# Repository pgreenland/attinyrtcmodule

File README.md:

# ATTinyRTCModule

This repository contains my attempt at a real-time clock (RTC) replacement, specially for the Mac SE/30, untested (yet should work :-P) on others, using the Microchip ATTiny85.

It's specifically aimed at SE/30's that have suffered damage to their RTC circuitry due to battery leaks.

It therefore doesn't require a battery, storing the PRAM contents in the ATTiny's integrated EEPROM.

It also doesn't require a crystal, using the ATTiny's integrated RC oscillator as its clock source.

It should work (although hasn't been tested) in a mac with a working RTC battery. If desired the EEPROM backup of the settings and time can be disabled via commenting out the definition `ENABLE_EEPROM`.

An effort has been made to limit the EEPROM writes. With only updates being written, and update only being considered when the RTC is marked as read-only by the host. However it isn't clear how long the EEPROM will last in the ATTiny's using this approach. Time will tell.

It's based on the good work by other folks:

https://www.reddit.com/r/VintageApple/comments/91e5cf/couldnt_find_a_replacement_for_the_rtcpram_chip/
https://pastebin.com/baPZ4nN4
https://github.com/quorten/macsehw/blob/master/firmware/rtc/MacRTC.c

The ATTiny85 was identified previously as a candidate for a drop-in replacement for some of the classic Mac family of RTC chips.

Previous versions of the firmware focused on the Mac Plus, which has a serial clock of between 1 and 20Khz (based on comments in the code).

The Mac SE/30 has a serial clock of 250Khz, requiring a substantial rewrite to get things working.

This version makes use of the universal serial interface module (USI) to ensure the original timing of the Apple RTC is always met.

My original drop-in replacement attempt [ATTinyRTC](https://github.com/pgreenland/attinyrtc) worked but was often a little close to violating the protocol timing. Using the USI module these problems are avoided and the timings exhibited by the original Apple RTC module are met.

See my blog for additional notes on how the software works / its development:

[New Timepiece for a Classic Mac - Part 1](http://www.quantulum.co.uk/blog/new-timepiece-for-a-classic-mac-part-1/)

[New Timepiece for a Classic Mac - Part 2](http://www.quantulum.co.uk/blog/new-timepiece-for-a-classic-mac-part-2/)

## Hardware

PCB may be ordered from yoru favorite supplier.

The BOM for this project was ordered from RS Components in the UK and consists of the following:

| **Reference** | **Part**                                                                                           | **Quantity** | **RS Part No** |
|---------------|----------------------------------------------------------------------------------------------------|--------------|----------------|
| U1            | Microchip ATTINY85-20SU, 8bit AVR Microcontroller, ATtiny85, 20MHz, 8 kB Flash, 8-Pin EIAJ SOIC    | 1            | 133-1674       |
| Y1            | Abracon 16MHz Crystal Unit ±20ppm SMD 4-Pin 3.2 x 2.5 x 0.8mm                                      | 1            | 171-2803       |
| C1,C2         | KEMET, 0805 (2012M) 18pF Multilayer Ceramic Capacitor MLCC 50V dc ±5% , SMD C0805C180J5GACTU       | 2            | 648-0935       |
| C3            | KYOCERA AVX, 0805 (2012M) 100nF Multilayer Ceramic Capacitor MLCC 50V dc ±10% , SMD 08055C104KAT2A | 1            | 464-6688       |

## Building

1. Ensure avg-gcc, cmake, make and avrdude are installed.

2. Build with cmake
   ```
   cd software
   mkdir build
   cd build
   cmake ..
   make
   ```

3. Flash
   ```
   make upload
   make upload_eeprom
   ```

4. Set fuses
   ```
   make fuses
   ```

### Note

The programmer I'm using is a usbasp programmer, search eBay for USBasp, they all seem pretty much the same. Remember to head over to [USBasp](https://www.fischl.de/usbasp/) to drop them a tip. Alternatively any programmer supported by avrdude can be selected via configuration in the CMake file.

If flashing using the external pins, remember that PB0 and PB1 are swapped (I definately didn't make that mistake).

As part of setting fuses the reset pin is reconfigured as GPIO.

Once this has been done the only way to re-program the chip is by using high voltage programming.

During development, as a workaround I've been re-assigning one of the unused crystal pins to fullfil the role of the PB5, with the help of a small adapter. Thereby allowing standard ICSP programming with no high voltage funny business required.

After the initial programming I found [this guide](https://www.electronics-lab.com/recover-bricked-attiny-using-arduino-as-high-voltage-programmer/) helpful. Using a spare Arduino and minimal components to rewrite the fuses using HV programming, such that the reset pin is again enabled and regular ICSP programming can be performed again.

If resetting fuses using the external pins, note that PB0 and PB1 are swapped as noted above. Also note that PB3 is not accessible via the headers and must be accessed directly on the ATTiny.

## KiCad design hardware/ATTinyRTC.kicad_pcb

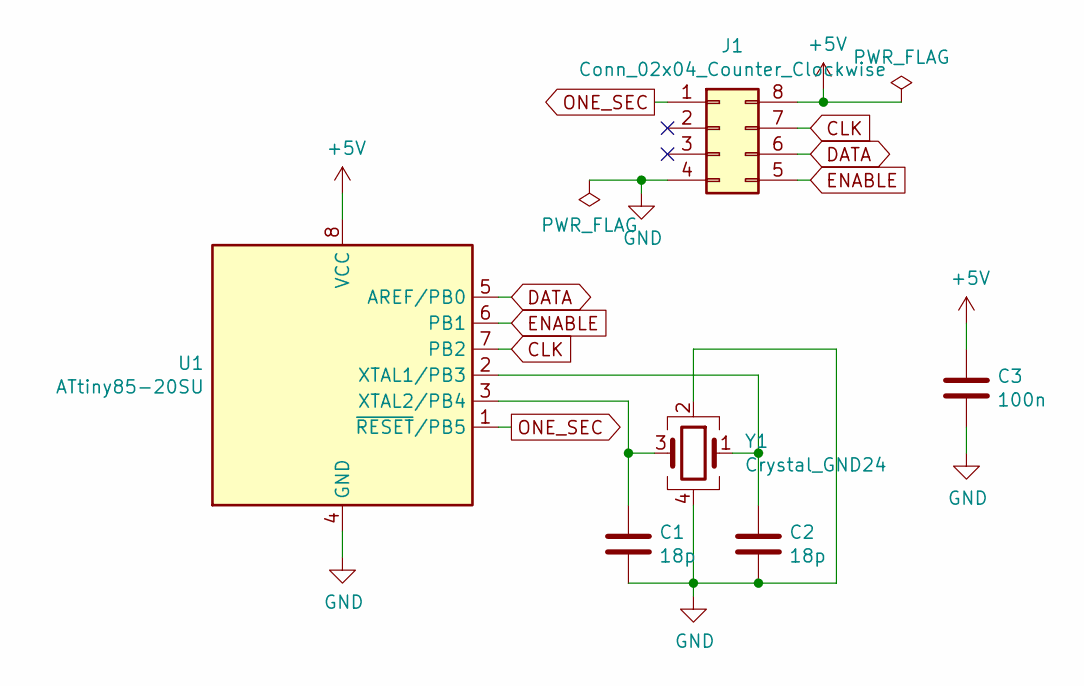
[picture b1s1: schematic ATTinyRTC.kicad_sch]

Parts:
C1, C2: 18p; C_0805_2012Metric
C3: 100n; C_0805_2012Metric
J1: Conn_02x04_Counter_Clockwise; DIP-8_W7.62mm
U1: ATtiny85-20SU; SOIC-8W_5.3x5.3mm_P1.27mm
Y1: Crystal_GND24; Crystal_SMD_Abracon_ABM8G-4Pin_3.2x2.5mm

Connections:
+5V: C3.1, J1.8, U1.8 (VCC)
CLK: J1.7, U1.7 (PB2)
DATA: J1.6, U1.5 (AREF/PB0)
ENABLE: J1.5, U1.6 (PB1)
GND: C1.2, C2.2, C3.2, J1.4, U1.4 (GND), Y1.2, Y1.4
unnamed: C1.1, U1.3 (XTAL2/PB4), Y1.3
unnamed: C2.1, U1.2 (XTAL1/PB3), Y1.1
ONE_SEC: J1.1, U1.1 (~RESET/PB5)

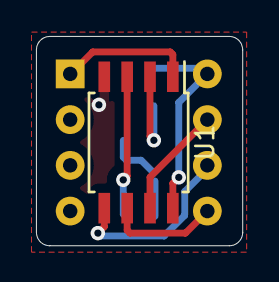
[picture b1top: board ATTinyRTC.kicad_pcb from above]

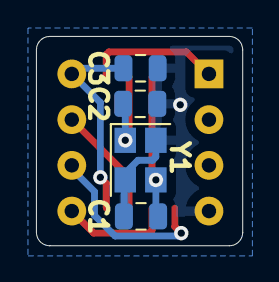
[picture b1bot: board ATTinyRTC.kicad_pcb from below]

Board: 2 copper layers, 11.5 x 11.6 mm, 6 parts (4 on the bottom side), 8 nets.

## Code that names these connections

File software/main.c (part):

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/* Define to have write only test register readable, returning 0xA5 and 0x5A on alternate reads */
//#define TEST_REG_READ_DUMMY_VALUE

/* Define to output timing pulses on PB3 */
//#define TIMING_ENABLED

/* ---------------------- */
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/*
RTC Pinout -> ATTiny85 pinout
              __  __
 1SEC (PB5) -|1 \/ 8|- VCC
XTAL1 (PB3) -|2    7|- (PB2) RTC.CLK
XTAL2 (PB4) -|3    6|- (PB1) RTC.DATA
        GND -|4____5|- (PB0) !RTC

Note that as the USI hardware is required, RTC.DATA and !RTC (enable) must be swapped.
*/
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} uSeconds_t;

/* Define pins */
static const uint8_t uiPinData = PB0;
static const uint8_t uiPinEnable = PB1;
static const uint8_t uiPinOneSec = PB5;

/* Hijack one of the crystal pins for some logic analyzer snoopage */
#ifdef TIMING_ENABLED
static const uint8_t uiPinTiming = PB3;
#endif

/* Define pin change interrupts to match enable pin above */
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
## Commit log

2022-12-29 Initial work on replacement RTC module.
2023-09-23 Add delay at startup before enabling interrupts. Save clock every 60s
2024-03-04 Write after timeout, rather than tracking write protect register. Use 8-bit counter for timeouts. Start with write protection disabled.
